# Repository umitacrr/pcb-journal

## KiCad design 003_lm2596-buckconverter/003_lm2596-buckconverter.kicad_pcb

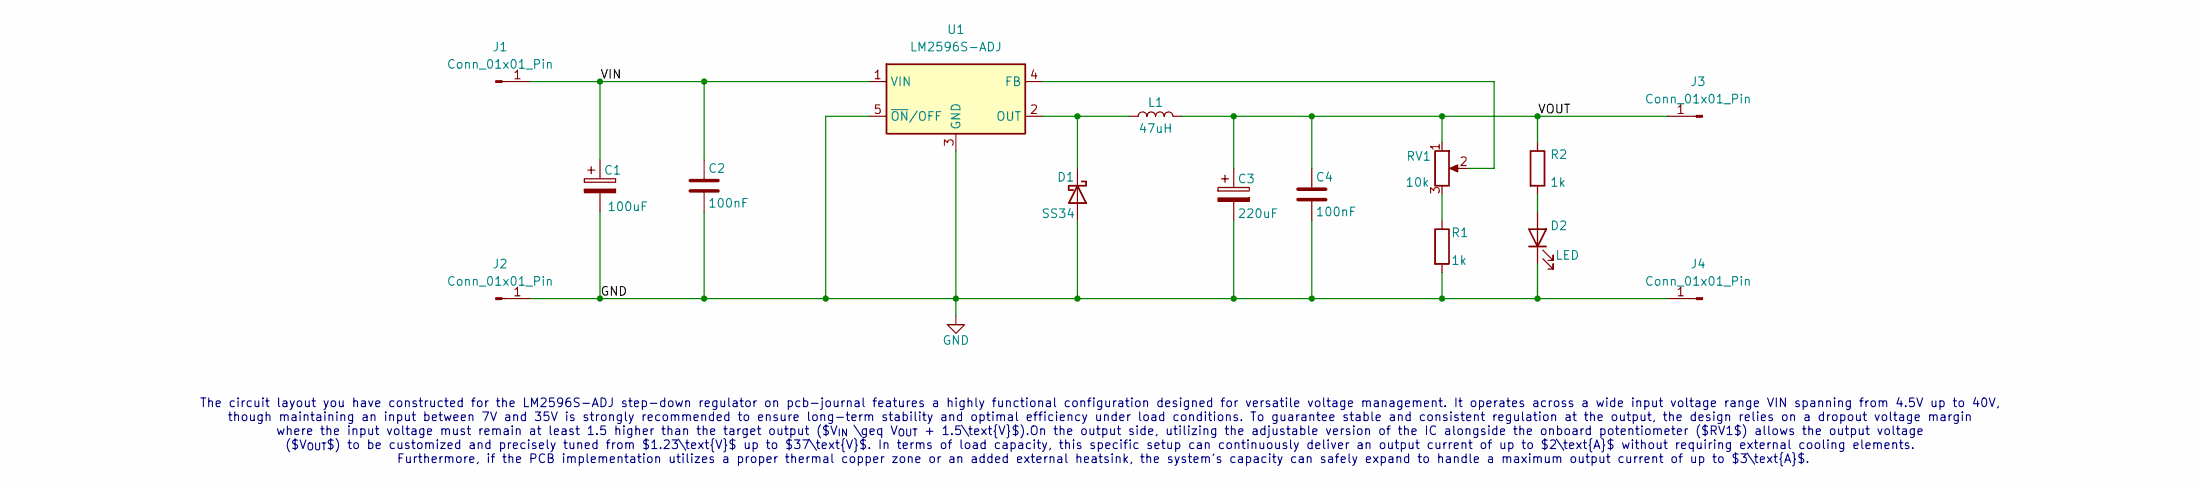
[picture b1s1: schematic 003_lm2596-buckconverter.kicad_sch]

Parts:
C1: 100uF; CP_Elec_8x10
C2, C4: 100nF; C_0603_1608Metric
C3: 220uF; CP_Elec_8x10
D1: SS34; D_SMA
D2: LED; LED_0603_1608Metric
J1, J2, J3, J4: Conn_01x01_Pin; PinSocket_1x01_P2.54mm_Vertical
L1: 47uH; L_Bourns_SRR1208_12.7x12.7mm
R1, R2: 1k; R_0603_1608Metric
RV1: 10k; Potentiometer_Bourns_3296Y_Vertical
U1: LM2596S-ADJ; TO-263-5_TabPin3

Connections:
/VIN: C1.1, C2.1, J1.1 (Pin_1_1), U1.1 (VIN)
/VOUT: C3.1, C4.1, J3.1 (Pin_1_1), L1.2, R2.1, RV1.1
GND: C1.2, C2.2, C3.2, C4.2, D1.2 (A), D2.1 (K), J2.1 (Pin_1_1), J4.1 (Pin_1_1), R1.2, U1.3 (GND), U1.5 (~ON/OFF)
unnamed: D1.1 (K), L1.1, U1.2 (OUT)
unnamed: D2.2 (A), R2.2
unnamed: R1.1, RV1.3
unnamed: RV1.2, U1.4 (FB)

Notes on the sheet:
The circuit layout you have constructed for the LM2596S-ADJ step-down regulator on pcb-journal features a highly functional configuration designed for versatile voltage management. It operates across a wide input voltage range VIN spanning from 4.5V up to 40V, though maintaining an input between 7V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

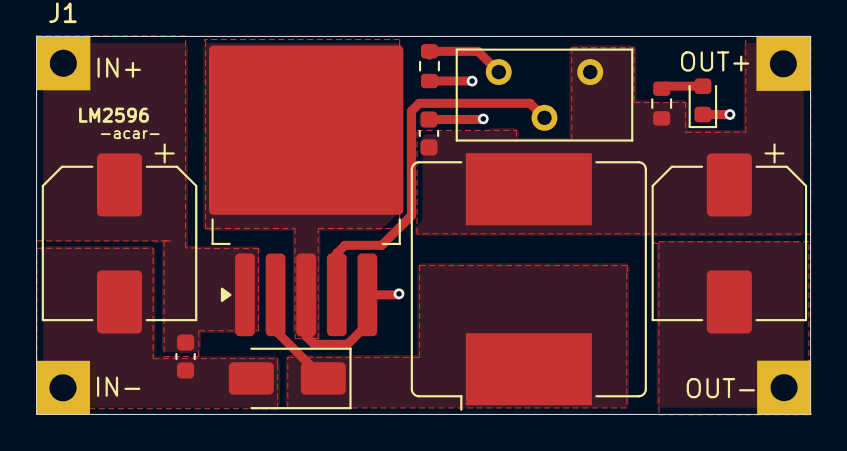
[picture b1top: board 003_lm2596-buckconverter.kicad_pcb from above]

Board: 2 copper layers, 43.0 x 21.0 mm, 15 parts (0 on the bottom side), 7 nets.

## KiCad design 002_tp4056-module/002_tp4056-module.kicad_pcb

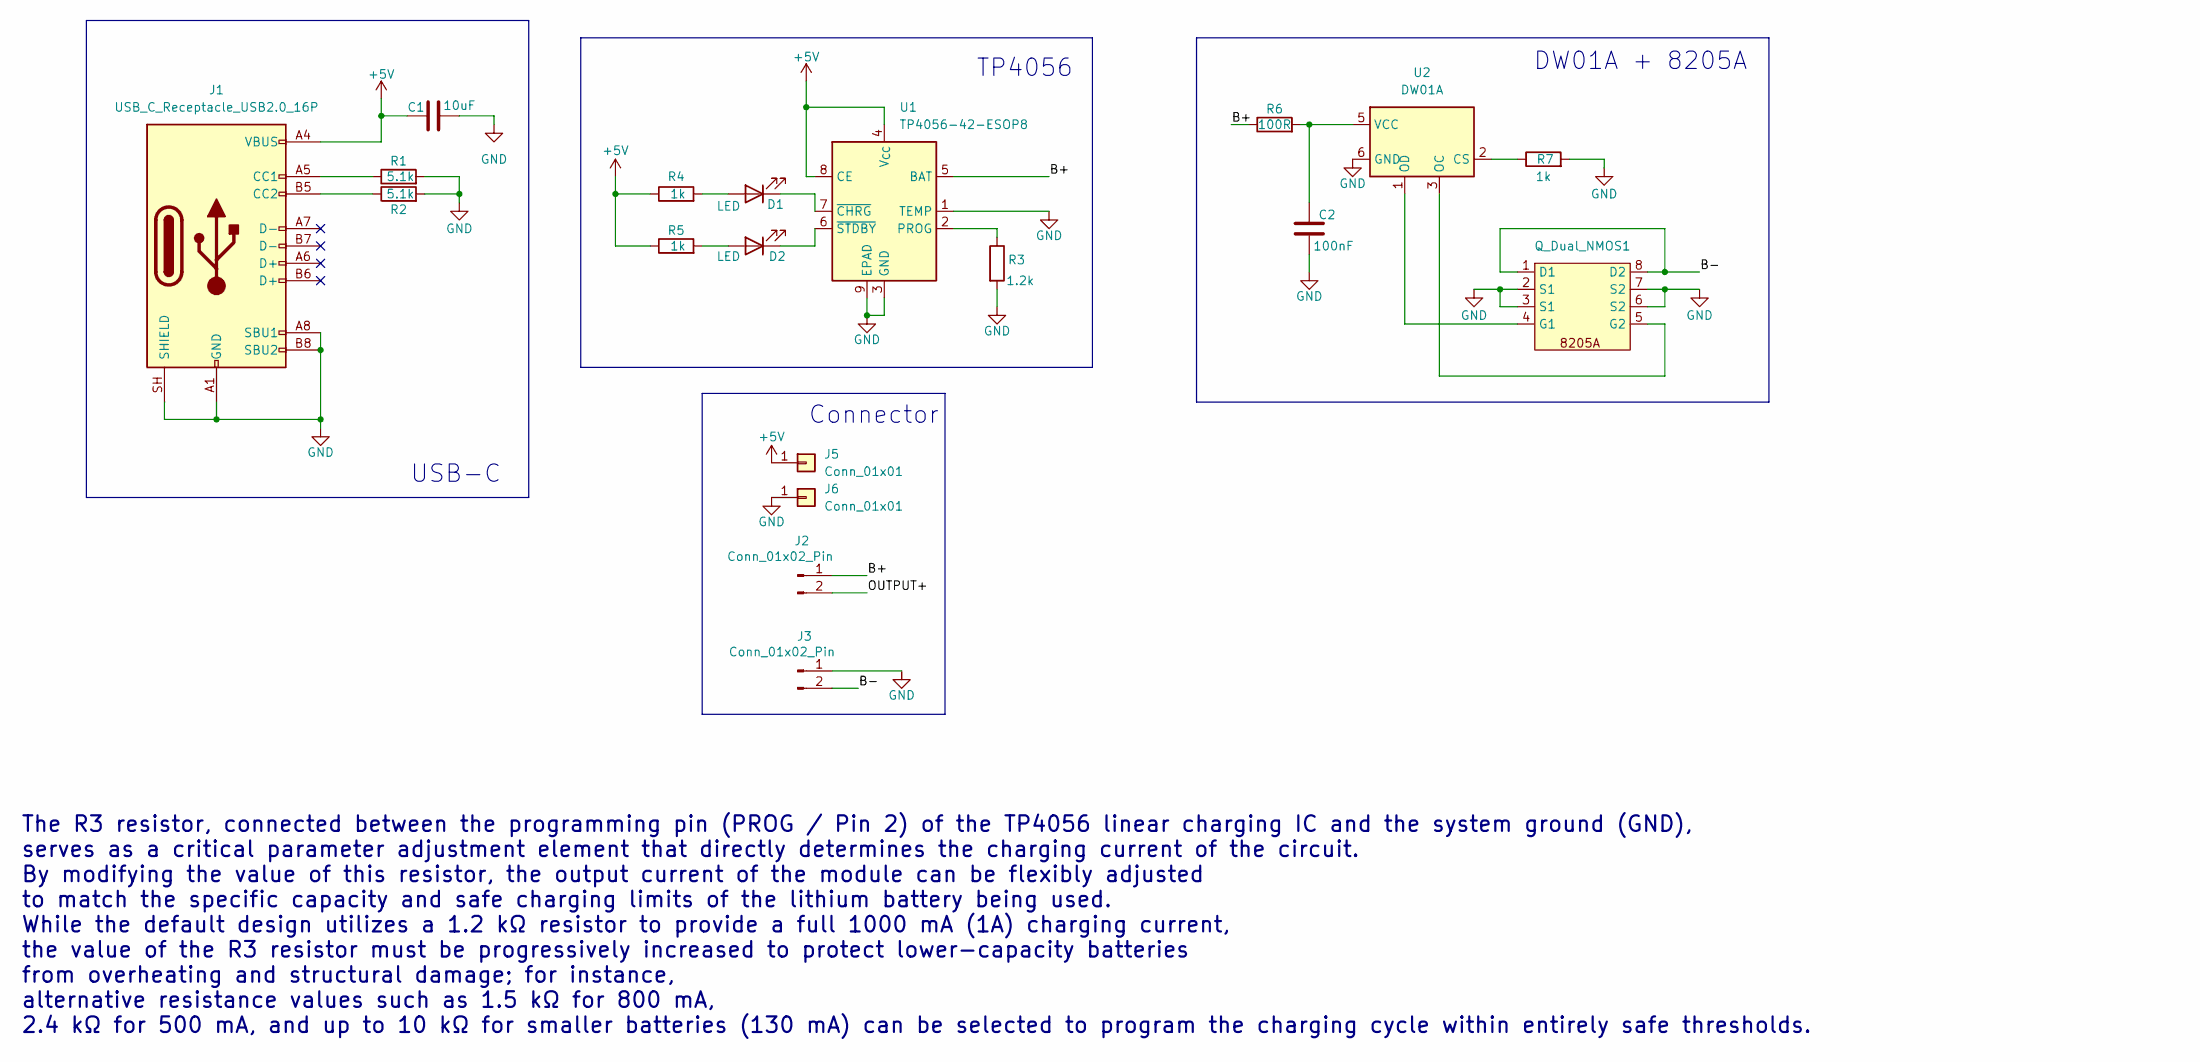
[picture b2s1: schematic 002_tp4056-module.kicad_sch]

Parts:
C1: 10uF; C_0402_1005Metric
C2: 100nF
D1, D2: LED; LED_0402_1005Metric
J1: USB_C_Receptacle_USB2.0_16P; USB_C_Receptacle_HRO_TYPE-C-31-M-12
J2, J3: Conn_01x02_Pin; PinHeader_1x02_P2.54mm_Vertical
J5, J6: Conn_01x01; PinHeader_1x01_P2.54mm_Vertical
Q_Dual_NMOS1: 8205A
R1, R2: 5.1k; R_0402_1005Metric
R3: 1.2k; R_0402_1005Metric
R4, R5, R7: 1k; R_0402_1005Metric
R6: 100R; R_0402_1005Metric
U1: TP4056-42-ESOP8; SOIC-8-1EP_3.9x4.9mm_P1.27mm_EP2.41x3.3mm_ThermalVias
U2: DW01A; SOT-23-6

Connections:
+5V: C1.1, J1.A4 (VBUS), J1.A9 (VBUS), J1.B4 (VBUS), J1.B9 (VBUS), J5.1 (Pin_1_1), R4.1, R5.1, U1.4 (V_{CC}), U1.8 (CE)
/B+: J2.1, R6.1, U1.5 (BAT)
/B-: J3.2, Q_Dual_NMOS1.1 (D1), Q_Dual_NMOS1.8 (D2)
/OUTPUT+: J2.2
GND: C1.2, C2.2, J1.A1 (GND), J1.A8 (SBU1), J1.A12 (GND), J1.B1 (GND), J1.B8 (SBU2), J1.B12 (GND), J1.SH (SHIELD), J3.1, J6.1 (Pin_1_1), Q_Dual_NMOS1.2 (S1), Q_Dual_NMOS1.3 (S1), Q_Dual_NMOS1.6 (S2), Q_Dual_NMOS1.7 (S2), R1.2, R2.2, R3.2, R7.2, U1.1 (TEMP), U1.3 (GND), U1.9 (EPAD), U2.6 (GND)
unnamed: D1.2 (A), R4.2
unnamed: D1.1 (K), U1.7 (~CHRG)
unnamed: D2.2 (A), R5.2
unnamed: D2.1 (K), U1.6 (~STDBY)
unnamed: J1.A5 (CC1), R1.1
unnamed: J1.B5 (CC2), R2.1
unnamed: Q_Dual_NMOS1.4 (G1), U2.1 (OD)
unnamed: Q_Dual_NMOS1.5 (G2), U2.3 (OC)
unnamed: R3.1, U1.2 (PROG)
unnamed: R7.1, U2.2 (CS)
unnamed: C2.1, R6.2, U2.5 (VCC)

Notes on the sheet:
TP4056
DW01A + 8205A
The R3 resistor, connected between the programming pin (PROG / Pin 2) of the TP4056 linear charging IC and the system ground (GND), serves as a critical parameter adjustment element that directly determines the charging current of the circuit. By modifying the value of this resistor, the output cur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
USB-C
Connector

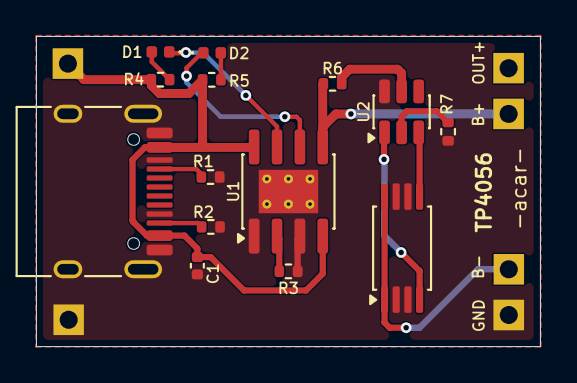
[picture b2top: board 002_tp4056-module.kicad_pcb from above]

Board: 2 copper layers, 28.0 x 17.2 mm, 18 parts (0 on the bottom side), 15 nets.

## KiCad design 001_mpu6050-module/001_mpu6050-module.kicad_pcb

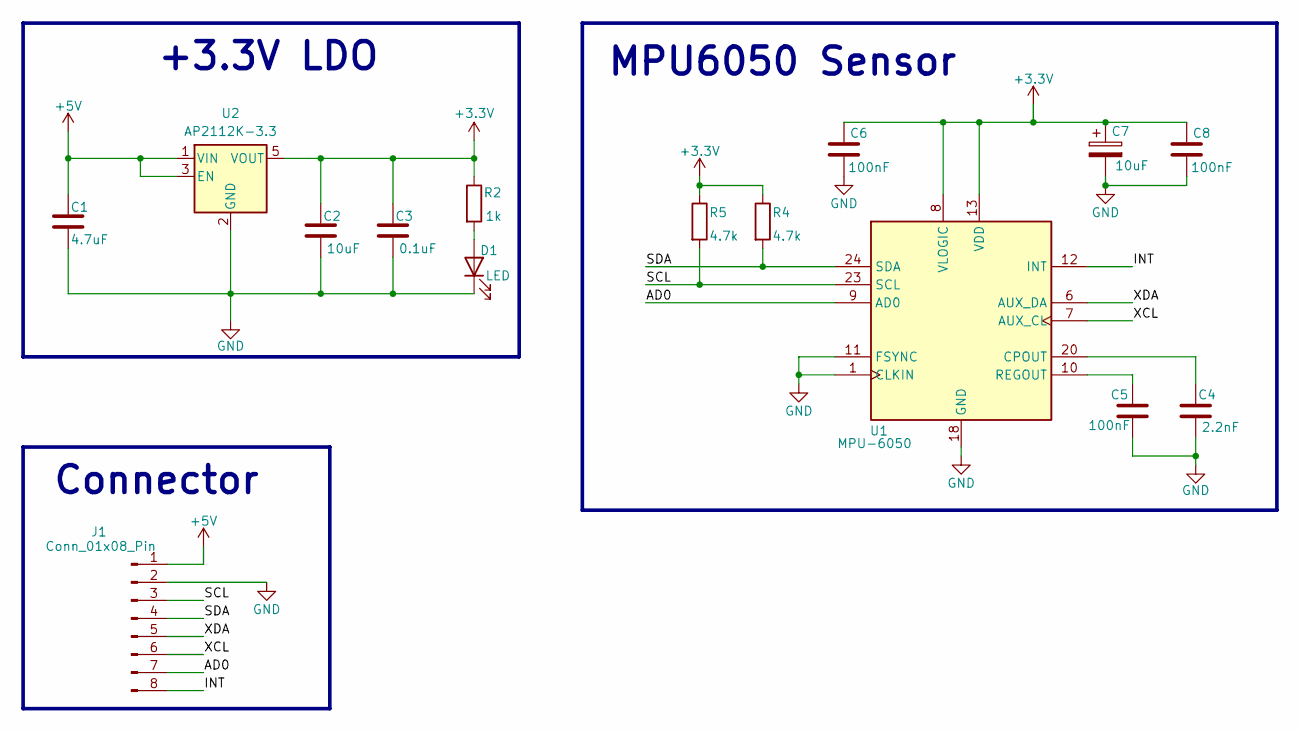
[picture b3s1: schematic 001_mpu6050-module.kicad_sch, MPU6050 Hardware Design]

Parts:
C1: 4.7uF; C_0603_1608Metric
C2: 10uF; C_0603_1608Metric
C3: 0.1uF; C_0603_1608Metric
C4: 2.2nF; C_0603_1608Metric
C5, C6, C8: 100nF; C_0603_1608Metric
C7: 10uF; CP_EIA-3216-10_Kemet-I
D1: LED; LED_0603_1608Metric
J1: Conn_01x08_Pin; PinHeader_1x08_P2.54mm_Vertical
R2: 1k; R_0603_1608Metric
R4, R5: 4.7k; R_0603_1608Metric
U1: MPU-6050; InvenSense_QFN-24_4x4mm_P0.5mm
U2: AP2112K-3.3; SOT-23-5

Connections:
+3.3V: C2.1, C3.1, C6.1, C7.1, C8.1, R2.1, R4.1, R5.1, U1.8 (VLOGIC), U1.13 (VDD), U2.5 (VOUT)
+5V: C1.1, J1.1, U2.1 (VIN), U2.3 (EN)
/AD0: J1.7, U1.9 (AD0)
/INT: J1.8, U1.12 (INT)
/SCL: J1.3, R5.2, U1.23 (SCL)
/SDA: J1.4, R4.2, U1.24 (SDA)
/XCL: J1.6, U1.7 (AUX_CL)
/XDA: J1.5, U1.6 (AUX_DA)
GND: C1.2, C2.2, C3.2, C4.2, C5.1, C6.2, C7.2, C8.2, D1.1 (K), J1.2, U1.1 (CLKIN), U1.11 (FSYNC), U1.18 (GND), U2.2 (GND)
unnamed: D1.2 (A), R2.2
unnamed: C4.1, U1.20 (CPOUT)
unnamed: C5.2, U1.10 (REGOUT)

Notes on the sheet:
Connector
MPU6050 Sensor
+3.3V LDO

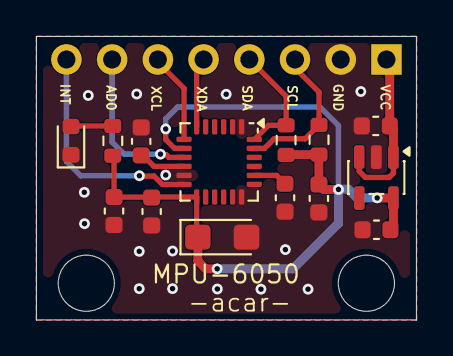
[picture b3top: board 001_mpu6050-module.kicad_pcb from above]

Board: 2 copper layers, 21.1 x 15.7 mm, 15 parts (0 on the bottom side), 12 nets.
